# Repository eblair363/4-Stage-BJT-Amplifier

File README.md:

# 4-Transistor BJT Amplifier PCB

A discrete BJT amplifier — Darlington emitter follower into a cascode gain stage,
four PN2222A transistors on a +24 V supply — originally designed in PSpice for a
course, then re-implemented as a KiCad PCB. The first physical build was dead-bug
on copper clad and it died on test day from an under-rated resistor. This repo is
the rebuild: the same circuit, with the failure understood, the bias problem found
in simulation before ordering, and the whole thing laid out on a proper board.
The board and parts are ordered; nothing is assembled or measured yet, so every
number here is simulated and labeled as such.

*3D render of the KiCad layout. Not a photo — the board has not arrived yet.*

## Specification

| Spec | Target | Simulated | Measured |
|---|---|---|---|
| Voltage gain | ≥ 35 V/V | 38.8 V/V at 1 MHz | pending bring-up |
| Gain at test frequency | ≥ 35 V/V at 10 MHz | 38.1 V/V | pending bring-up |
| Input impedance | ≥ 300 kΩ | 934 kΩ at low frequency | pending bring-up |
| Power into 1 kΩ load | ≥ 10 mW | 11.0 mW at 127 mV input | pending bring-up |
| −3 dB bandwidth | ≥ 50 MHz | 64.5 MHz unloaded | pending bring-up |
| Supply current | — | 36.7 mA | pending bring-up |
| THD at 10 MHz | — | 5.4 % | pending bring-up |

Simulated figures are from ngspice (`sim/spice/amp_sanity_ngspice.cir`) using the
classic PSpice Q2N2222 model. The input impedance figure is from the original
PSpice run; it is a low-frequency number and falls below 300 kΩ around 70 kHz.

The bandwidth target started at 200 MHz, which assumed a breadboard
implementation. That was not practical at these frequencies, so the target was
revised to 50 MHz and the design was pushed to about 60 MHz in simulation to
leave margin for losses on the bench.

## Circuit

**Stage 1 — Q1/Q2 Darlington emitter follower.** Biased through R1 (1 MΩ). The
Darlington multiplies the input resistance by both betas, which is what buys the
≥ 300 kΩ input impedance. Gain is just under 1; this stage exists to not load the
source.

**Stage 2 — cascode.** Q4 is the common-emitter gain device, Q3 is common-base
stacked on top of it. Q3 holds Q4's collector at a nearly fixed voltage, so Q4's
collector-base capacitance sees almost no voltage swing. That kills the Miller
multiplication that would otherwise dominate the high-frequency rolloff, and it
is the reason a 60 MHz bandwidth is reachable with parts this cheap.

R7 (1 kΩ) is the collector load, C4 couples to the 1 kΩ load resistor R9, which
lives on the board so the amplifier can be tested without hanging a load off the
SMA jack.

| PSpice name | KiCad ref | Value | Note |
|---|---|---|---|
| Rb1 | R1 | 1 MΩ | stage 1 bias |
| Re | R2 | 910 Ω, 2 W | the part that killed the first build |
| R3a | R3 | 10 kΩ | Q4 bias divider, top |
| R3b | R4 | 360 Ω | Q4 bias divider, bottom — bench-tuned |
| R4a | R5 | 100 kΩ | Q3 base divider, top |
| Rb4 | R6 | 22 kΩ | Q3 base divider, bottom |
| Rc | R7 | 1 kΩ 1% | collector load |
| Re3 | R8 | 10 Ω | Q4 emitter degeneration |
| RLoad | R9 | 1 kΩ 1% | on-board load |
| C2 | C1 | 100 nF | input coupling |
| C4 | C2 | 100 nF | interstage coupling |
| C1 | C3 | 100 nF | Q3 base bypass |
| C3 | C4 | 100 nF | output coupling |

Also on the board: C5 (10 µF) and C6–C8 (100 nF) for supply decoupling, J1/J2 SMA
jacks, J3 screw terminal for +24 V, and TP1–TP5 bias test points.

## The design story

### Test-day failure

The first build was dead-bug on copper clad. It was destroyed during testing.

Root cause, found afterward: R2, the stage-1 emitter resistor, carries the whole
Darlington bias current. At 910 Ω and about 24 mA that is

    P = I²R = (0.024)² × 910 ≈ 0.52 W

It was a 1/4 W part. It ran at roughly twice its rating, overheated, and took the
board with it. Nothing in the simulation flagged this, because a PSpice resistor
has no power rating — the number was right there in the operating point the whole
time and I never divided it out.

The board was rebuilt dead-bug afterward, on my own time, and it worked. I did not
record numbers from that rebuild, so nothing from it is quoted here.

### What the PCB does about it

- R2 is now a 2 W part (KOA MOS2, 910 Ω), mounted raised off the board so it can
  shed heat into air instead of into the substrate
- supply decoupling: 10 µF plus 100 nF at the input, 100 nF at each stage
- TP1–TP5 test points on the bias nodes, so the DC state can be checked before a
  signal ever goes in
- solid ground plane on the bottom layer
- SMA jacks instead of clip leads, and the load resistor on the board

### Pre-order sanity check: the output was clipping

Before sending the board out, I re-ran the design in ngspice and LTspice and found
a second problem, quieter than the first one.

The output stage biased at about 6.6 mA. The most positive swing a common-emitter
stage can deliver is limited by that bias current into the AC load:

    V_peak(max) = I_bias × (R7 ∥ R9) = 6.6 mA × 500 Ω = 3.3 V

Getting 10 mW into 1 kΩ needs 4.47 V peak. So the positive half of the output ran
out of current before it reached the target. That is exactly the lopsided
+3 V / −5.2 V waveform in the original PSpice output-power plot, and why that run
read about 9.6 mW instead of 10 mW, with about 13 % distortion. I had read that
plot as "close enough" at the time. It was not close enough — it was clipping.

The fix is values only, no layout change:

| Part | Course design | PCB | Effect |
|---|---|---|---|
| R8 (Q4 emitter) | 9.1 Ω | 10 Ω | sets stage gain and degeneration |
| R4 (bias divider, bottom) | 330 Ω | 360 Ω | raises Q4 bias current |

That moves the output-stage bias from about 6.6 mA to about 10.6 mA, which puts
the positive swing limit above what 10 mW needs. Reproduced in ngspice:

| | R4 = 330, R8 = 9.1 | R4 = 360, R8 = 10 |
|---|---|---|
| Q4 bias current | 6.6 mA | 10.6 mA |
| Output swing | +3.02 V / −5.27 V | +4.08 V / −5.14 V |
| Power into 1 kΩ | 9.54 mW | 11.0 mW |
| THD at 10 MHz | 13.2 % | 5.4 % |
| Gain at 1 MHz | 37.1 V/V | 38.8 V/V |
| Supply current | 32.8 mA | 36.7 mA |

The schematic and the ordered BOM carry the fixed values. Swap the `.param` line
in the ngspice netlist back to `R4v=330 R8v=9.1` to reproduce the clipped case.

R4 is still marked bench-tuned, because this bias point is genuinely twitchy: it
is set by a sub-1 V divider working against one Vbe drop. A ±5 % part tolerance on
R4 moves the collector current by roughly ±25 %, and warming Q4 by 25 °C adds
roughly another 30 %. A resistor value is not a substitute for actually measuring
the node.

> **TODO:** full re-simulation of the as-built values with a second transistor
> model, with screenshots. The figures above are from a single-model ngspice run.

## Bring-up plan

Nothing below has been done yet.

1. **Set the bench supply to 24 V with a 50 mA current limit** before connecting
   anything. Expected draw is about 37 mA; anything near the limit means a fault.
2. **Check the DC test points with no input signal** against the table below.
3. **Tune R4** to bring Q3_C to its target. This is the trim that sets output
   headroom — too low and the positive half clips again, too high and the negative
   half does.
4. **Set the function generator to High-Z output mode.** In 50 Ω mode it will
   deliver half the amplitude it displays, which would make the gain read 2× low.
5. **Measure gain at 1 MHz and 10 MHz** with a properly compensated 10× probe.

### Expected DC test points (simulated, no signal)

| Test point | Node | Expected |
|---|---|---|
| Q2_E | stage-1 emitter | 21.6 V |
| Q4_B | Q4 base | 0.81 V |
| Q3_B | Q3 base | 3.37 V |
| Q4_C | Q4 collector | 2.67 V |
| Q3_C | output stage collector | 13.5 V — **R4 trim target** |

> **TODO:** measured column, once the board is populated.

## Measurement caveats

The output node sits at about 500 Ω (R7 ∥ R9). A 10× scope probe adds 10–15 pF
there, and that capacitance against 500 Ω forms a pole well below the amplifier's
own bandwidth. The bench will not measure 64 MHz, and that is the probe, not the
board:

| Probe capacitance | Gain at 1 MHz | Gain at 10 MHz | −3 dB bandwidth |
|---|---|---|---|
| none (ideal) | 38.8 | 38.1 | 64.5 MHz |
| 10 pF | 38.8 | 35.5 | 22.4 MHz |
| 15 pF | 38.8 | 33.3 | 16.6 MHz |

All simulated. A 1× probe or a length of coax into a 1 MΩ input is far worse —
roughly 115 pF — and would put the corner near 2 MHz. Gain at 1 MHz is unaffected,
so that is the honest number to compare against the 35 V/V spec.

## Status and roadmap

- [x] PSpice design, course version
- [x] Dead-bug build — destroyed on test day
- [x] Root cause found: R2 power rating
- [x] Dead-bug rebuild, worked (no numbers recorded)
- [x] KiCad schematic and layout, DRC clean
- [x] Pre-order simulation check, bias fix applied to the schematic
- [x] PCB ordered from JLCPCB
- [x] Parts ordered from DigiKey
- [ ] Board and parts arrive
- [ ] Assemble
- [ ] Bench bring-up: test points, R4 trim
- [ ] Measure gain, bandwidth, output power, input impedance
- [ ] Full re-simulation with a second transistor model, with screenshots
- [ ] Photos of the assembled board and scope captures

## Repository layout

```
hardware/   KiCad project (schematic, PCB, footprints)
sim/pspice/ original PSpice screenshots and parts list from the course design
sim/spice/  LTspice sanity netlist and its ngspice port
docs/       exported schematic, 3D renders, photos
fab/        gerbers, drill files, BOM
scripts/    export.sh, regenerates everything in docs/ and fab/
```

Regenerate all artifacts after a KiCad change:

```sh
./scripts/export.sh
```

Run the simulation:

```sh
ngspice -b sim/spice/amp_sanity_ngspice.cir
```

> **TODO:** `docs/photos/` is empty. Dead-bug build photo, assembled PCB, and
> scope captures go there.

## Tools

KiCad 10.0.5 (schematic, layout, fabrication output), PSpice (original course
design), LTspice and ngspice 47 (pre-order verification).

## Notes on the simulation files

`sim/spice/amp_sanity.cir` is the LTspice version: one analysis at a time, with
`.meas` cards read out of the SPICE error log. `sim/spice/amp_sanity_ngspice.cir`
is the ngspice port — `SINE(` becomes `SIN(`, and the `.meas` cards move into a
`.control` block so all three analyses run in a single pass.

`sim/pspice/` holds the original course-design screenshots. Two things to know
about them: `outputpower.png` is the **pre-fix** run showing the clipped ~9.6 mW
result, and a fourth screenshot (`schematicRe2_2kBiasPoints.png`) was removed
because it was mislabeled — it showed the 910 Ω bias numbers, not the 2.2 kΩ ones.

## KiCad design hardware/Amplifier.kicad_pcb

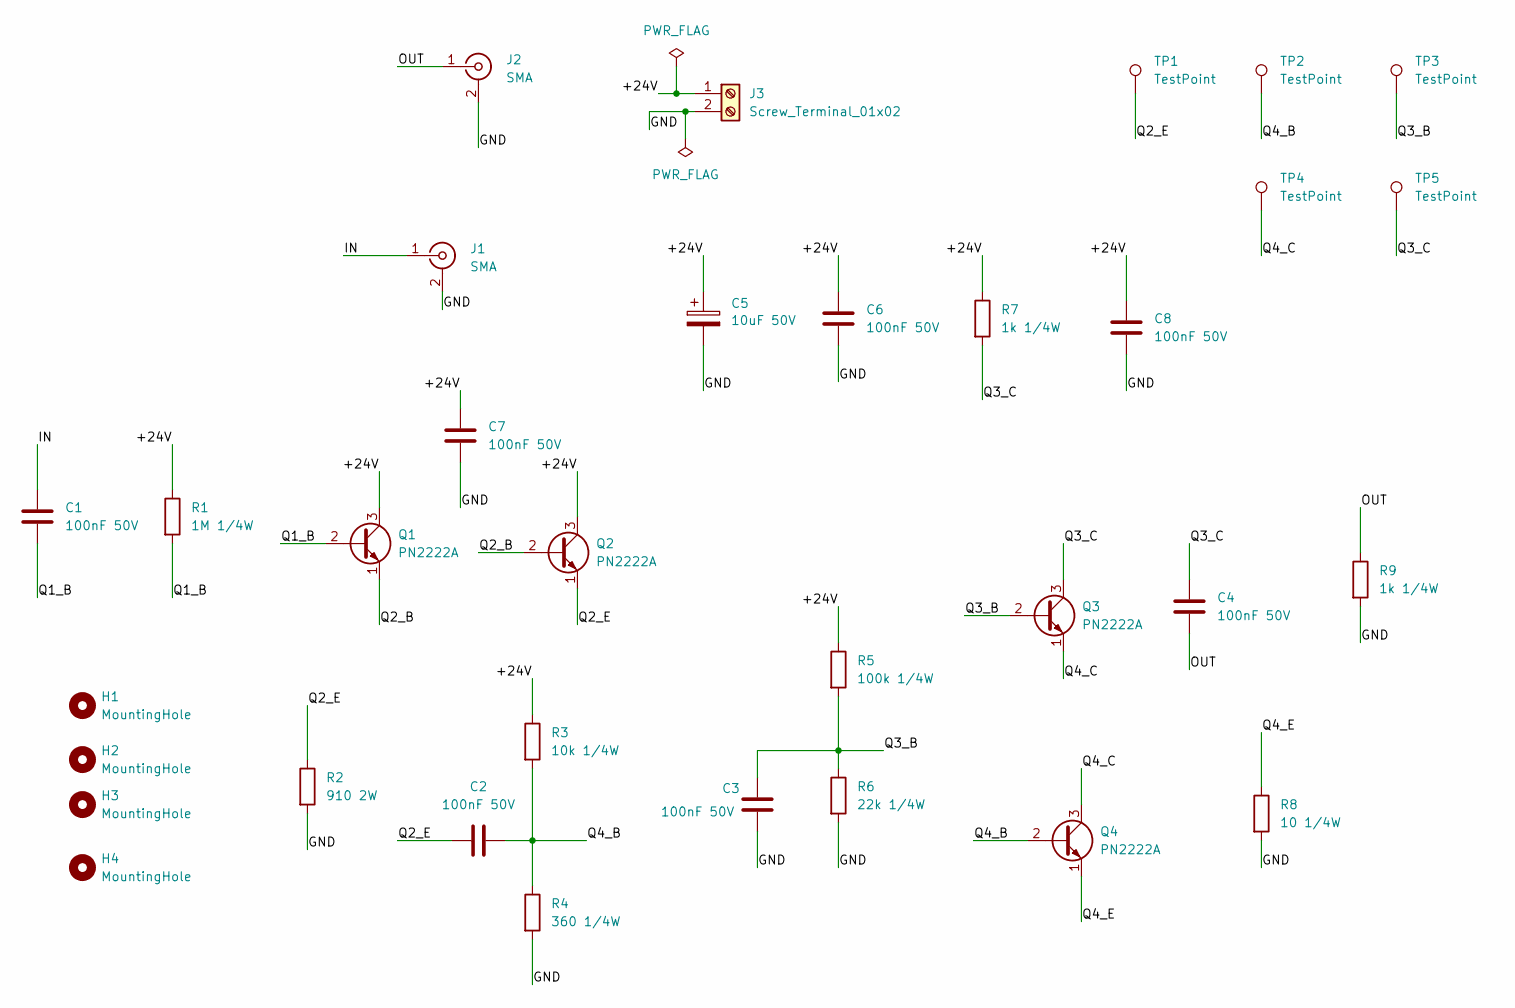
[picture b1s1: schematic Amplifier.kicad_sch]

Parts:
C1, C2, C3, C4, C6, C7, C8: 100nF 50V; C_Disc_D5.0mm_W2.5mm_P5.00mm
C5: 10uF 50V; CP_Radial_D6.3mm_P2.50mm
H1, H2, H3, H4: MountingHole; MountingHole_3.2mm_M3
J1, J2: SMA; SMA_Amphenol_132134_Vertical
J3: Screw_Terminal_01x02; TerminalBlock_Phoenix_MKDS-1,5-2-5.08_1x02_P5.08mm_Horizont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
Q1, Q2, Q3, Q4: PN2222A; TO-92_Inline_Wide
R1: 1M 1/4W; R_Axial_DIN0207_L6.3mm_D2.5mm_P10.16mm_Horizontal
R2: 910 2W; R_Axial_DIN0414_L11.9mm_D4.5mm_P20.32mm_Horizontal
R3: 10k 1/4W; R_Axial_DIN0207_L6.3mm_D2.5mm_P10.16mm_Horizontal
R4: 360 1/4W; R_Axial_DIN0207_L6.3mm_D2.5mm_P10.16mm_Horizontal
R5: 100k 1/4W; R_Axial_DIN0207_L6.3mm_D2.5mm_P10.16mm_Horizontal
R6: 22k 1/4W; R_Axial_DIN0207_L6.3mm_D2.5mm_P10.16mm_Horizontal
R7, R9: 1k 1/4W; R_Axial_DIN0207_L6.3mm_D2.5mm_P10.16mm_Horizontal
R8: 10 1/4W; R_Axial_DIN0207_L6.3mm_D2.5mm_P10.16mm_Horizontal
TP1, TP2, TP3, TP4, TP5: TestPoint; TestPoint_Keystone_5000-5004_Miniature

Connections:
/+24V: C5.1, C6.1, C7.1, C8.1, J3.1, Q1.3 (C), Q2.3 (C), R1.1, R3.1, R5.1, R7.1
/GND: C3.2, C5.2, C6.2, C7.2, C8.2, J1.2 (Ext), J2.2 (Ext), J3.2, R2.2, R4.2, R6.2, R8.2, R9.2
/IN: C1.2, J1.1 (In)
/OUT: C4.2, J2.1 (In), R9.1
/Q1_B: C1.1, Q1.2 (B), R1.2
/Q2_B: Q1.1 (E), Q2.2 (B)
/Q2_E: C2.1, Q2.1 (E), R2.1, TP1.1 (1_1)
/Q3_B: C3.1, Q3.2 (B), R5.2, R6.1, TP3.1 (1_1)
/Q3_C: C4.1, Q3.3 (C), R7.2, TP5.1 (1_1)
/Q4_B: C2.2, Q4.2 (B), R3.2, R4.1, TP2.1 (1_1)
/Q4_C: Q3.1 (E), Q4.3 (C), TP4.1 (1_1)
/Q4_E: Q4.1 (E), R8.1

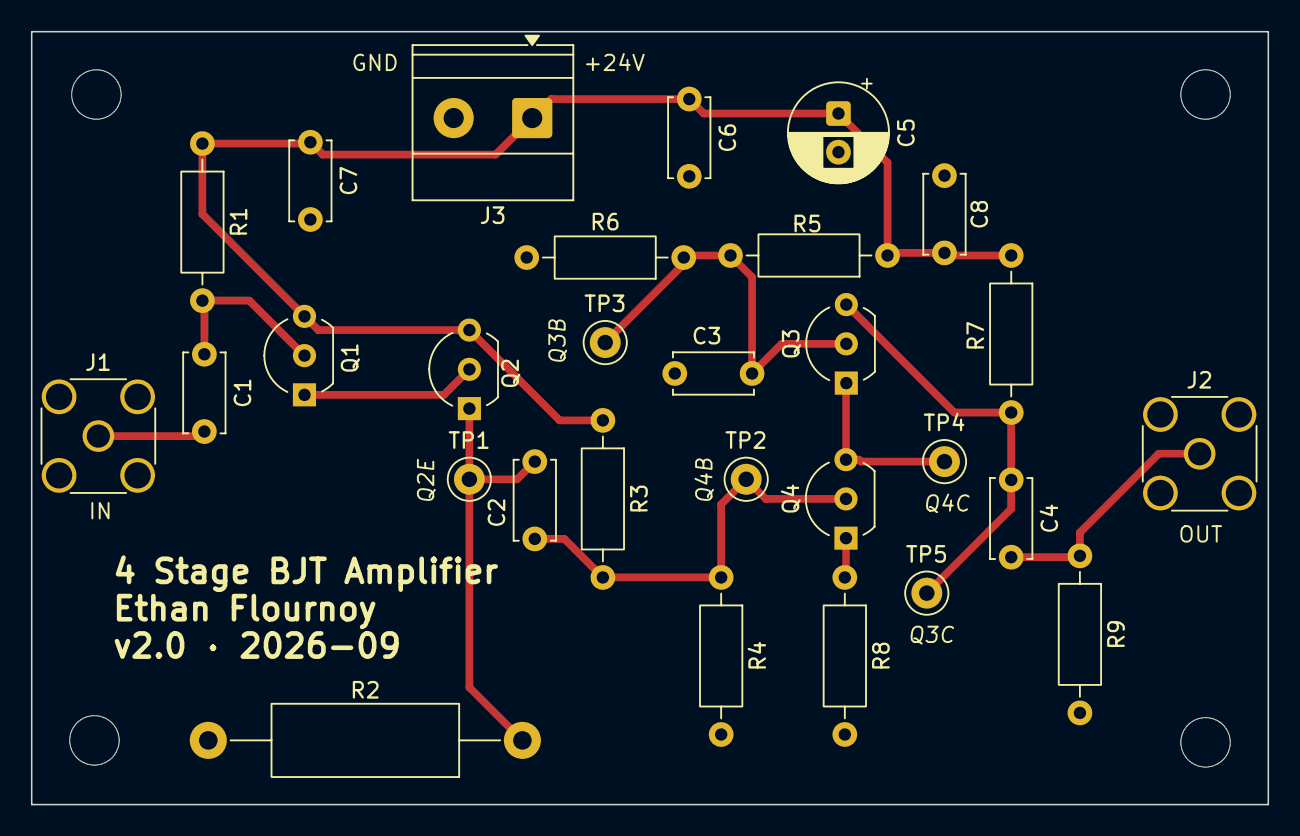
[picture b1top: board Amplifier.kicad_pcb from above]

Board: 2 copper layers, 80.0 x 50.0 mm, 33 parts (0 on the bottom side), 12 nets.
